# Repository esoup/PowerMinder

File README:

Power Minder project

README file

An Arduino IDE project built upon the DigiSpark for prototyping.
All elements of the design are under development

I am new to GitHub - excuse the mess as I learn.

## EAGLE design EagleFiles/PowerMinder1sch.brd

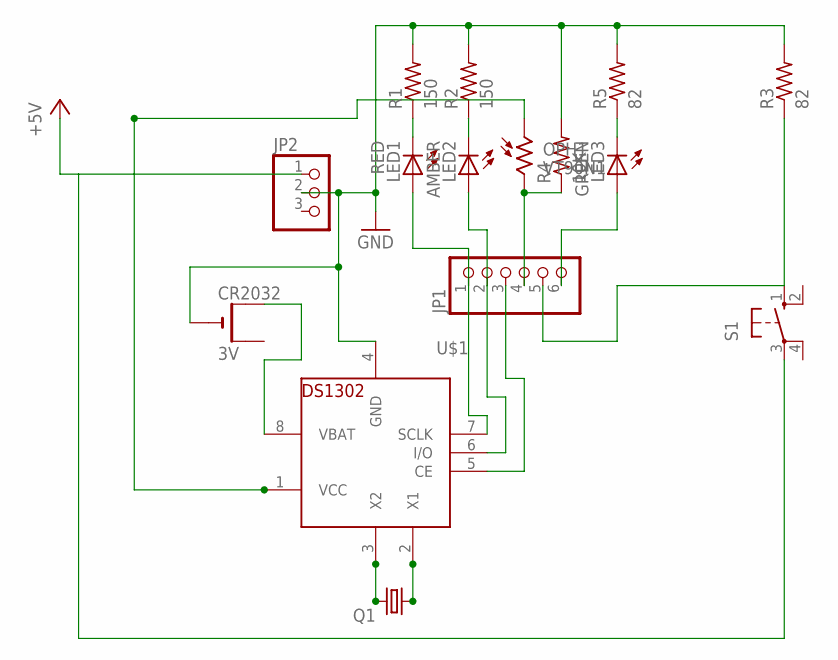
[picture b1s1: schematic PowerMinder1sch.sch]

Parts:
CR2032: 3V; CR2032-THRU
JP1: PINHD-1X6; 1X06
JP2: PINHD-1X3; 1X03
LED1: RED; LED5MM
LED2: AMBER; LED5MM
LED3: GREEN; LED5MM
OPH1: VT90N1; VT900
Q1: CRYSTALTC26H; TC26H
R1, R2: 150; 0207/12
R3, R5: 82; 0207/12
R4: 10K; 0207/12
S1: 10-XX; B3F-10XX
U$1: DS1302; DIL08-ROUND

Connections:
+5V: JP2.1, OPH1.1, S1.3, U$1.1 (VCC)
GND: CR2032.-, JP2.2, R1.2, R2.2, R3.2, R4.2, R5.2, U$1.4 (GND)
unnamed: JP1.1, LED1.A, U$1.7 (SCLK)
unnamed: JP1.2, LED2.A, U$1.6 (I/O)
unnamed: JP1.4, OPH1.2, R4.1
unnamed: JP1.6, LED3.A
unnamed: LED1.K (C), R1.1
unnamed: LED2.K (C), R2.1
unnamed: LED3.K (C), R5.1
unnamed: Q1.1, U$1.2 (X1)
unnamed: Q1.2, U$1.3 (X2)
unnamed: CR2032.+1 (+), U$1.8 (VBAT)
unnamed: JP1.5, R3.1, S1.1 (S)
unnamed: JP1.3, U$1.5 (CE)

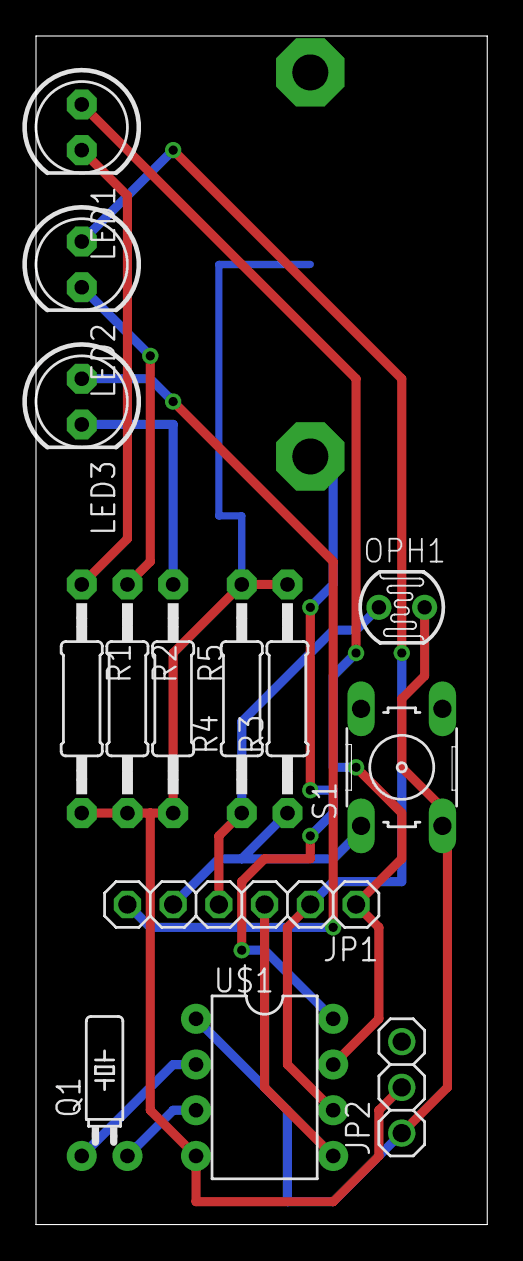
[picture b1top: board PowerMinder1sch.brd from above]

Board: 2 copper layers, 25.1 x 66.0 mm, 15 parts (1 on the bottom side), 14 nets.

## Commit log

2013-12-18 README 1.0 uploaded
    Time to get this thing started.
2013-12-19 Moved code from GoogleDoc
2013-12-19 Added "get" functions in calendar class
2013-12-19 Added calendar-creation methods and Doxygen generation
2013-12-19 Added test/display for Calendar function
2013-12-19 Added to the 'clean' target
2013-12-21 Implemented Calendar::check function
2013-12-24 Something to start with.
    Added an INO scetch PowerMinder.ino in a PowerMinder folder (to make
    Arduino environment happy). Added rtc.h and rtc.cpp to the same folder
    - seems anything in the folder gets loaded and maybe not following the
    #include as expected.
2014-02-03 Moved SRC files added possible hardware plc eagle files
2014-02-03 Spelling correction
2014-02-06 DigiSparkArduino now compiles the code.
    No Calendar.cpp code incorporated into main program yet. Concentrated
    on compilation.
    For Eagle files made micro adjustments to component positions. Do not
    yet trust the Eagle files as they are untested and unverified. Three
    prototype are being built to verify the design.
2014-02-21 Fixed board
    Proto BRD now probably functional. Original button now goes high and
    added a resistor to GND. Value for R are all TBD. Battery holder will
    need to be moved as it may hit the LED pins.
2014-02-21 Removed Eagle backups
2014-02-21 New ignore file
2014-02-21 Proto board V2
    Layout changes - may help with battery position. Resistors moved to
    help with routing - needs more work - suits the prototype need for now.
    Expect Proto v4 to be the board that is stable enough for the project
    to make you own.
2014-03-29 Created LED class and cleaned up main program
2014-03-29 Added button management class
2014-03-30 Implemented asymmetrical LED blinking. Debounced button. Implemented jump-to-programming mode at boot time.
2014-03-30 Added light sensor management class. Implemented light sensor test Minimized variable sizes in button and LED classes.
2014-04-05 Moved button sampling back to interrupt service to minimize sampling.
2014-04-05 Removed all RTC code. Recalibrated light sensor after fixing Pin 3 configuration bug. Added strobe test.
